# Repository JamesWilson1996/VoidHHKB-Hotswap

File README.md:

# VoidHHKB-Hotswap

## Ordering from JLCPCB

1) Head to the [JLCPCB order page](https://cart.jlcpcb.com/quote).

2) Upload the `VoidHHKB-Hotswap.zip` file in `production/`.

3) Set the quantity of the PCBs you want made.

4) Set your desired PCB parameters. Here are some suggested parameters: (Everything else can be kept at their default)

- PCB Color: **Purple**
- Surface Finish: **ENIG**
- Remove Order Number: **Yes**   

5) Enable the PCB Assembly option at the bottom, and set the following parameters:

- PCBA Type: **Standard**
- Assembly Side: **Bottom**

6) Press `Confirm` at the bottom or `NEXT` on the right to get to the next page.

7) Click `NEXT` to get to the Bill of Materials tab.

8) Click `Add BOM File` and select the `bom.csv` file in `production/`.

9) Click `Add CPL File` and select the `positions.csv` file in `production/`. Click `Process BOM & CPL` to proceed.

10) You should be presented with a list of all the components and quantities needed. Double check there are no missing components. If there are, you will have to find substitute components for it. Click `NEXT` to proceed.

11) You should be presented with a view of the PCB and its components. You will most likely need to rotate the Hotswap sockets manually. Click `NEXT` to proceed.

12) You should see a breakdown of the price for the PCBs you want to order. Select `Keyboard - HS Code 847330` under `Office Appliance Accessories` for the Product Description.

13) Save to cart, and pay for it!

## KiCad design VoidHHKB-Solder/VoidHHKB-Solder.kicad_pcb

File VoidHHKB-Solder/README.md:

# VoidHHKB-Solder

## Ordering from JLCPCB

1) Head to the [JLCPCB order page](https://cart.jlcpcb.com/quote).

2) Upload the `VoidHHKB-Hotswap.zip` file in `production/`.

3) Set the quantity of the PCBs you want made.

4) Set your desired PCB parameters. Here are some suggested parameters: (Everything else can be kept at their default)

- PCB Color: **Purple**
- Surface Finish: **ENIG**
- Remove Order Number: **Yes**   

5) Enable the PCB Assembly option at the bottom, and set the following parameters:

- PCBA Type: **Standard**
- Assembly Side: **Bottom**

6) Press `Confirm` at the bottom or `NEXT` on the right to get to the next page.

7) Click `NEXT` to get to the Bill of Materials tab.

8) Click `Add BOM File` and select the `bom.csv` file in `production/`.

9) Click `Add CPL File` and select the `positions.csv` file in `production/`. Click `Process BOM & CPL` to proceed.

10) You should be presented with a list of all the components and quantities needed. Double check there are no missing components. If there are, you will have to find substitute components for it. Click `NEXT` to proceed.

11) You should be presented with a view of the PCB and its components. Click `NEXT` to proceed.

12) You should see a breakdown of the price for the PCBs you want to order. Select `Keyboard - HS Code 847330` under `Office Appliance Accessories` for the Product Description.

13) Save to cart, and pay for it!

## Flashing Firmware

1) To do...

## Using VIA

Temp instructions until I get around to merging files into QMK repo...
1) To do...

## Build your own firmware

1) To do...

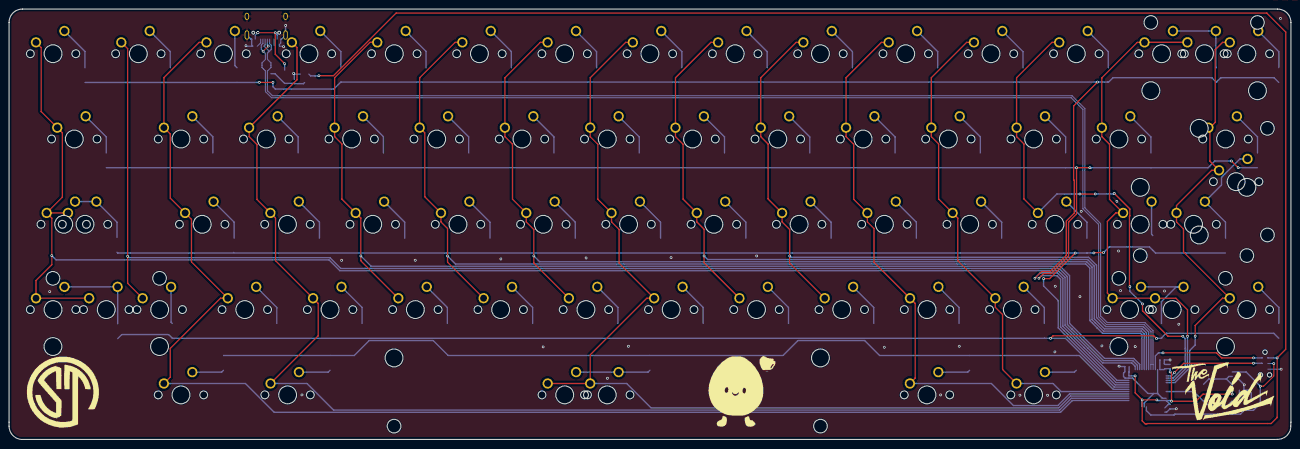
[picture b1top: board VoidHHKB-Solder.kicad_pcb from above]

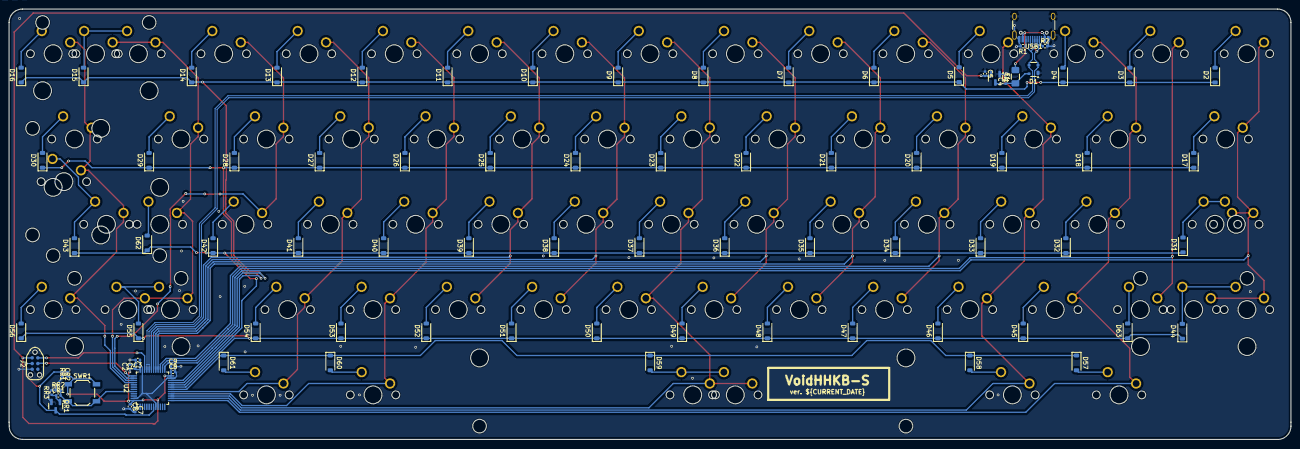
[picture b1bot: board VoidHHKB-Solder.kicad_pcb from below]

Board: 2 copper layers, 286.4 x 96.1 mm, 160 parts (86 on the bottom side), 95 nets.

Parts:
C1, C8: 4.7uF; C_0402_1005Metric
C2, C3, C7, C9: 100nF; C_0402_1005Metric
C4, C5, C6: 1uF; C_0402_1005Metric
CR1: 10uF; C_0402_1005Metric
CR2: 1uF; C_0402_1005Metric
D1: PRTR5V0U2X; SOT-143
D2, D3, D4, D5, D6, D7, D8, D9, D10, D11, D12, D13, D14, D15, D16, D17, D18, D19, D20, D21, D22, D23, D24, D25, D26, D27, D28, D29, D30, D31, D32, D33, D34, D35, D36, D37, D38, D39, D40, D41, D42, D43, D44, D45, D46, D47, D48, D49, D50, D51, D52, D53, D54, D55, D56, D57, D58, D59, D60, D61, D62, D63: 1N4148W; D_SOD-123
F1: 500mA; Fuse_1206_3216Metric_Pad1.42x1.75mm_HandSolder
J2: TC2030_SWD; CON_TC2030_outlined
MX1, MX2, MX3, MX4, MX5, MX6, MX7, MX8, MX9, MX10, MX11, MX12, MX13, MX14, MX15, MX16, MX17, MX18, MX19, MX20, MX21, MX22, MX23, MX24, MX25, MX26, MX27, MX28, MX29, MX31, MX32, MX33, MX34, MX35, MX36, MX37, MX38, MX39, MX40, MX41, MX42, MX43, MX44, MX45, MX46, MX47, MX48, MX49, MX50, MX51, MX52, MX53, MX54, MX55, MX56, MX57, MX58, MX59, MX60, MX61, MX63, MX64, MX66, MX67, MX68: MX_SW_HS; SW_MX_1u
MX30: MX_SW_HS; SW_MX_1.75u_STP_1.25
MX62: MX_SW_HS; SW_MX_1.75u
MX65: NUHS; SW_MX_1u
QR1: 2N7002; SOT-23
R1, R2: 5k1; R_0402_1005Metric
RR1: 33k; R_0402_1005Metric
RR2: 10k; R_0402_1005Metric
RR3: 100k; R_0402_1005Metric
S1: 2.25u ANSI Enter; STAB_MX_2.25u
S2: 2.25 LShift; STAB_MX_2.25u
S3: 6u Spacebar; STAB_MX_6u_New
S4: 2u Backspace; STAB_MX_2u
S5: ISO Enter; STAB_MX_ISO-ROT
S6: 2.75 RShift; STAB_MX_2.75u
SWR1: TS-1187A-B-A-B; SW_SPST_TL3342
U1: XC6206P332MR; SOT-23
U2: STM32F072CBT6; LQFP-48_7x7mm_P0.5mm
USB1: USB_C_Receptacle_USB2.0_16P; USB_C_Receptacle_HRO_TYPE-C-31-M-12

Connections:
+3V3: C1.1, C2.1, C3.1, C5.2, C6.1, C7.1, C8.1, C9.1, J2.1 (VCC), RR1.1, SWR1.1, U1.2 (VO), U2.9 (VDDA), U2.24 (VDD), U2.36 (VDDIO2), U2.48 (VDD)
+5V: C4.1, D1.4 (VCC), F1.1, U1.3 (VI)
/CC1: R2.1, USB1.A5 (CC1)
/CC2: R1.1, USB1.B5 (CC2)
BOOT0: CR1.2, RR2.2, SWR1.2, U2.44 (BOOT0)
D+: D1.3 (I/O2), U2.33 (PA12), USB1.A6 (D+), USB1.B6 (D+)
D-: D1.2 (I/O1), U2.32 (PA11), USB1.A7 (D-), USB1.B7 (D-)
GND: C1.2, C2.2, C3.2, C4.2, C5.1, C6.2, C7.2, C8.2, C9.2, CR2.2, D1.1 (GND), J2.5 (GND), QR1.2 (S), R1.2, R2.2, RR2.1, RR3.2, U1.1 (GND), U2.8 (VSSA), U2.23 (VSS), U2.35 (VSS), U2.47 (VSS), USB1.A1 (GND), USB1.A12 (GND), USB1.B1 (GND), USB1.B12 (GND), USB1.S1 (SHIELD)
NRST: CR2.1, J2.3 (~RST), QR1.3 (D), RR1.2, U2.7 (NRST)
unnamed: D2.2 (A), MX1.2
unnamed: D3.2 (A), MX2.2
unnamed: D4.2 (A), MX3.2
unnamed: D5.2 (A), MX4.2
unnamed: D6.2 (A), MX5.2
unnamed: D7.2 (A), MX6.2
unnamed: D8.2 (A), MX7.2
unnamed: D9.2 (A), MX8.2
unnamed: D10.2 (A), MX9.2
unnamed: D11.2 (A), MX10.2
unnamed: D12.2 (A), MX11.2
unnamed: D13.2 (A), MX12.2
unnamed: D14.2 (A), MX13.2
unnamed: D15.2 (A), MX14.2, MX63.2
unnamed: D16.2 (A), MX15.2
unnamed: D17.2 (A), MX16.2
unnamed: D18.2 (A), MX17.2
unnamed: D19.2 (A), MX18.2
unnamed: D20.2 (A), MX19.2
unnamed: D21.2 (A), MX20.2
unnamed: D22.2 (A), MX21.2
unnamed: D23.2 (A), MX22.2
unnamed: D24.2 (A), MX23.2
unnamed: D25.2 (A), MX24.2
unnamed: D26.2 (A), MX25.2
unnamed: D27.2 (A), MX26.2
unnamed: D28.2 (A), MX27.2
unnamed: D29.2 (A), MX28.2
unnamed: D30.2 (A), MX29.2
unnamed: D31.2 (A), MX30.2, MX62.2
unnamed: D32.2 (A), MX31.2
unnamed: D33.2 (A), MX32.2
unnamed: D34.2 (A), MX33.2
unnamed: D35.2 (A), MX34.2
unnamed: D36.2 (A), MX35.2
unnamed: D37.2 (A), MX36.2
unnamed: D38.2 (A), MX37.2
unnamed: D39.2 (A), MX38.2
unnamed: D40.2 (A), MX39.2
unnamed: D41.2 (A), MX40.2
unnamed: D42.2 (A), MX41.2
unnamed: D43.2 (A), MX42.2, MX64.2
unnamed: D44.2 (A), MX43.2, MX67.2
unnamed: D45.2 (A), MX44.2
unnamed: D46.2 (A), MX45.2
unnamed: D47.2 (A), MX46.2
unnamed: D48.2 (A), MX47.2
unnamed: D49.2 (A), MX48.2
unnamed: D50.2 (A), MX49.2
unnamed: D51.2 (A), MX50.2
unnamed: D52.2 (A), MX51.2
unnamed: D53.2 (A), MX52.2
unnamed: D54.2 (A), MX53.2
unnamed: D55.2 (A), MX54.2, MX68.2
unnamed: D56.2 (A), MX55.2
unnamed: D57.2 (A), MX56.2
unnamed: D58.2 (A), MX57.2
unnamed: D59.2 (A), MX58.2, MX61.2
unnamed: D60.2 (A), MX59.2
unnamed: D61.2 (A), MX60.2
unnamed: D62.2 (A), MX65.2
unnamed: D63.2 (A), MX66.2
unnamed: CR1.1, QR1.1 (G), RR3.1
PA3: MX3.1, MX17.1, MX31.1, MX44.1, MX56.1, U2.13 (PA3)
PA4: MX4.1, MX18.1, MX32.1, MX45.1, MX57.1, U2.14 (PA4)
PA5: MX8.1, MX22.1, MX36.1, MX49.1, MX58.1, MX61.1, U2.15 (PA5)
PA6: MX11.1, MX25.1, MX39.1, MX52.1, MX59.1, U2.16 (PA6)
PA7: MX12.1, MX26.1, MX40.1, MX53.1, MX60.1, U2.17 (PA7)
PA8: MX7.1, MX21.1, MX35.1, MX48.1, U2.29 (PA8)
PA9: MX9.1, MX23.1, MX37.1, MX50.1, U2.30 (PA9)
PA10: MX10.1, MX24.1, MX38.1, MX51.1, U2.31 (PA10)
PA15: MX13.1, MX27.1, MX41.1, U2.38 (PA15)
PB0: D57.1 (K), D58.1 (K), D59.1 (K), D60.1 (K), D61.1 (K), U2.18 (PB0)
PB1: D44.1 (K), D45.1 (K), D46.1 (K), D47.1 (K), D48.1 (K), D49.1 (K), D50.1 (K), D51.1 (K), D52.1 (K), D53.1 (K), D54.1 (K), D55.1 (K), D56.1 (K), D63.1 (K), U2.19 (PB1)
PB2: D31.1 (K), D32.1 (K), D33.1 (K), D34.1 (K), D35.1 (K), D36.1 (K), D37.1 (K), D38.1 (K), D39.1 (K), D40.1 (K), D41.1 (K), D42.1 (K), D43.1 (K), D62.1 (K), U2.20 (PB2)
PB3: MX14.1, MX28.1, MX54.1, MX63.1, MX65.1, MX68.1, U2.39 (PB3)
PB4: MX15.1, MX29.1, MX42.1, MX55.1, MX64.1, U2.40 (PB4)
PB10: D17.1 (K), D18.1 (K), D19.1 (K), D20.1 (K), D21.1 (K), D22.1 (K), D23.1 (K), D24.1 (K), D25.1 (K), D26.1 (K), D27.1 (K), D28.1 (K), D29.1 (K), D30.1 (K), U2.21 (PB10)
PB11: D2.1 (K), D3.1 (K), D4.1 (K), D5.1 (K), D6.1 (K), D7.1 (K), D8.1 (K), D9.1 (K), D10.1 (K), D11.1 (K), D12.1 (K), D13.1 (K), D14.1 (K), D15.1 (K), D16.1 (K), U2.22 (PB11)
PB12: MX1.1, MX16.1, MX30.1, MX43.1, MX62.1, MX67.1, U2.25 (PB12)
PB13: MX2.1, MX66.1, U2.26 (PB13)
PB14: MX5.1, MX19.1, MX33.1, MX46.1, U2.27 (PB14)
PB15: MX6.1, MX20.1, MX34.1, MX47.1, U2.28 (PB15)
SWCLK: J2.4 (SWCLK), U2.37 (PA14)
SWDIO: J2.2 (SWDIO), U2.34 (PA13)
VBUS: F1.2, USB1.A4 (VBUS), USB1.A9 (VBUS), USB1.B4 (VBUS), USB1.B9 (VBUS)

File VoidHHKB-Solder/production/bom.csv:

Designator,Footprint,Quantity,Value,LCSC Part #
"C1, C8",0402,2,4.7uF,C23733
"C2, C3, C7, C9",0402,4,100nF,C1525
"C4, C5, C6, CR2",0402,4,1uF,C52923
CR1,0402,1,10uF,C15525
D1,SOT-143,1,PRTR5V0U2X,C2827688
"D10, D11, D12, D13, D14, D15, D16, D17, D18, D19, D2, D20, D21, D22, D23, D24, D25, D26, D27, D28, D29, D3, D30, D31, D32, D33, D34, D35, D36, D37, D38, D39, D4, D40, D41, D42, D43, D44, D45, D46, D47, D48, D49, D5, D50, D51, D52, D53, D54, D55, D56, D57, D58, D59, D6, D60, D61, D62, D63, D7, D8, D9",D_SOD-123,62,1N4148W,
F1,1206,1,500mA,C69688
"MX1, MX10, MX11, MX12, MX13, MX14, MX15, MX16, MX17, MX18, MX19, MX2, MX20, MX21, MX22, MX23, MX24, MX25, MX26, MX27, MX28, MX29, MX3, MX31, MX32, MX33, MX34, MX35, MX36, MX37, MX38, MX39, MX4, MX40, MX41, MX42, MX43, MX44, MX45, MX46, MX47, MX48, MX49, MX5, MX50, MX51, MX52, MX53, MX54, MX55, MX56, MX57, MX58, MX59, MX6, MX60, MX61, MX63, MX64, MX66, MX67, MX68, MX7, MX8, MX9",SW_MX_1u,65,MX_SW_HS,
MX30,SW_MX_1.75u_STP_1.25,1,MX_SW_HS,
MX62,SW_MX_1.75u,1,MX_SW_HS,
MX65,SW_MX_1u,1,NUHS,
QR1,SOT-23,1,2N7002,C8545
"R1, R2",0402,2,5k1,C25905
RR1,0402,1,33k,C25779
RR2,0402,1,10k,C25744
RR3,0402,1,100k,C25741
S4,STAB_MX_2u,1,2u Backspace,
S5,STAB_MX_ISO-ROT,1,ISO Enter,
SWR1,SW_SPST_TL3342,1,TS-1187A-B-A-B,C318884
U1,SOT-23,1,XC6206P332MR,C5446
U2,LQFP-48_7x7mm_P0.5mm,1,STM32F072CBT6,C81720
USB1,USB_C_Receptacle_HRO_TYPE-C-31-M-12,1,USB_C_Receptacle_USB2.0_16P,C165948

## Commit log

2025-02-04 Initial Commit with all files for VoidHHKB-Hotswap
2025-02-04 Removed redundant files
2025-02-04 Added images and updated readme
2025-02-04 Updated repo and readme with firmware and instructions for flashing.
2025-02-04 Removed unnecessary files.
2025-02-21 Removed switch sockets that can't be used due to plate limitations.
2025-03-04 Added Solder PCB
2025-03-04 Added solder pcb readme
2025-03-04 Updated Solder PCB. Fix designators and add labels to silk screen.
2025-03-06 Rearrange repo. Individual dir for each type
2025-03-12 Updated firmware files
2025-03-12 Updated solder readme
2025-03-12 Add Solder PCB option (#6)
    * Added Solder PCB
    * Added solder pcb readme
    * Updated Solder PCB. Fix designators and add labels to silk screen.
    * Rearrange repo. Individual dir for each type
    * Updated firmware files
    * Updated solder readme
